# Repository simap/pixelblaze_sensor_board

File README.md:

Pixelblaze Sensor Expansion Board
-------------------

* A microphone and signal processing with frequency magnitude data ranging from 37Hz-10KHz designed to work in very loud environments
* A 3-axis 16G accelerometer
* An ambient light sensor
* 5 analog inputs that can be used with potentiometers or other analog inputs

[For sale on Tindie](https://www.tindie.com/products/12158/)! Pick up this board and/or a Pixelblaze! Make cool sound-reactive LED things, or get one and hack the firmware!

I hope you find this useful or interesting. Maybe you hack your board? I'd be stoked to hear about it! Roll your own? Great! Turn it into a robot brain? Awesome!

Shout out to Sparkfun, their boards were used in the initial prototype, and their Eagle files were really helpful!

Shout out to [https://github.com/pyrohaz/STM32F0-PCD8544GraphicAnalyzer](https://github.com/pyrohaz/STM32F0-PCD8544GraphicAnalyzer) which does similar FFT stuff with a similar processor, even shares the fixed point FFT code in common!

Non-Pixelblaze Usage
-------------------
Looking to use this with an Arduino or Teensy or something? You just need a free serial port at 115200 baud.

The protocol is fairly simple:

1. Each frame starts with "SB1.0" including a null character (6 bytes).
2. The frequency information follows, as 32 x 16-bit unsigned integers.
3. Then is the audio energy average, max frequency magnitiude, max frequency Hz, all 3 as 16-bit unsigned ints.
4. Next the accelerometer information as 3 x 16-bit signed integers.
5. The data from the Light sensor is next, as a single 16-bit unsigned integer.
6. Followed by the 5 x 16-bit analog inputs (12-bit resolution, shifted up to 16 bits)
7. Finally "END" including a null character (4 bytes).

License Information
-------------------
The hardware files are released under [Creative Commons ShareAlike 4.0 International](https://creativecommons.org/licenses/by-sa/4.0/) since the PCB is largely based off of Sparkfun boards with this license requirement.

Distributed as-is; no warranty is given.

The ElectroMage logo and wizard character is excluded from this license.

The software is released under The MIT License.

The MIT License

Copyright (c) 2018 Ben Hencke

Permission is hereby granted, free of charge, to any person obtaining a copy
of this software and associated documentation files (the "Software"), to deal
in the Software without restriction, including without limitation the rights
to use, copy, modify, merge, publish, distribute, sublicense, and/or sell
copies of the Software, and to permit persons to whom the Software is
furnished to do so, subject to the following conditions:

The above copyright notice and this permission notice shall be included in
all copies or substantial portions of the Software.

THE SOFTWARE IS PROVIDED "AS IS", WITHOUT WARRANTY OF ANY KIND, EXPRESS OR
IMPLIED, INCLUDING BUT NOT LIMITED TO THE WARRANTIES OF MERCHANTABILITY,
FITNESS FOR A PARTICULAR PURPOSE AND NONINFRINGEMENT. IN NO EVENT SHALL THE
AUTHORS OR COPYRIGHT HOLDERS BE LIABLE FOR ANY CLAIM, DAMAGES OR OTHER
LIABILITY, WHETHER IN AN ACTION OF CONTRACT, TORT OR OTHERWISE, ARISING FROM,
OUT OF OR IN CONNECTION WITH THE SOFTWARE OR THE USE OR OTHER DEALINGS IN
THE SOFTWARE.

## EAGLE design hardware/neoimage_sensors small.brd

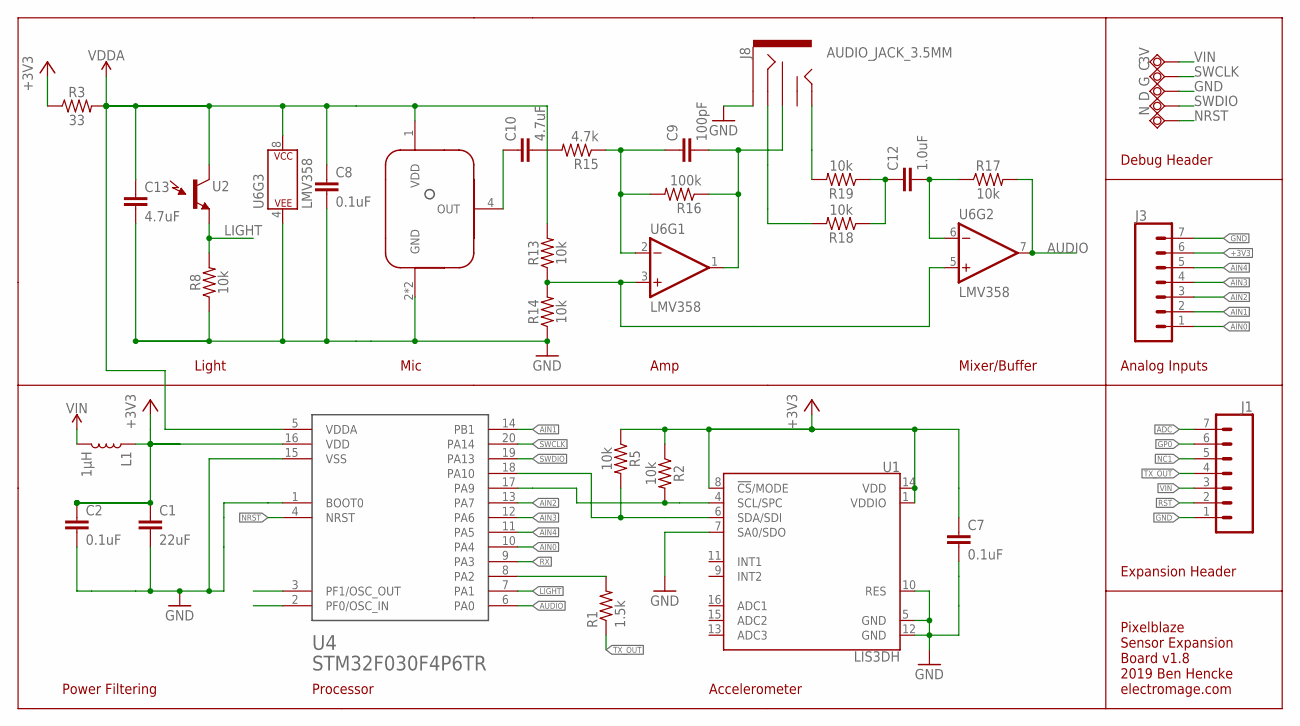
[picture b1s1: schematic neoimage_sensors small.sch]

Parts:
3V: TPSQTP18SQ; TP18SQ
C: TPSQTP18SQ; TP18SQ
C1: 22uF; 0805
C2, C7, C8: 0.1uF; 0603
C9: 100pF; 0603
C10, C13: 4.7uF; 0603
C12: 1.0uF; 0603
D: TPSQTP18SQ; TP18SQ
G: TPSQTP18SQ; TP18SQ
J1, J3: CONN_07LOCK; 1X07_LOCK
J8: AUDIO_JACK_3.5MM; AUDIO-JACK-KIT
L1: 1µH; 0805
N: TPSQTP18SQ; TP18SQ
R1: 1.5k; 0603
R2, R5, R8, R13, R14, R17, R18, R19: 10k; 0603
R3: 33; 0603
R15: 4.7k; 0603
R16: 100k; 0603
U1: LIS3DH; LGA-16-3X3
U2: LIGHT_SENSORALS; ALS-PT19
U4: STM32F030F4P6TR; TSSOP-20
U6: LMV358; SO08
U$3: MICROPHONE-MEMS; MICROPHONE-MEMS-3X3.75

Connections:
+3V3: C1.1, C2.1, C7.1, J3.6, L1.1, R2.1, R3.1, R5.1, U1.1 (VDDIO), U1.8 (!CS!/MODE), U1.14 (VDD), U4.16 (VDD)
ADC: J1.7
AIN0: J3.1, U4.10 (PA4)
AIN1: J3.2, U4.14 (PB1)
AIN2: J3.3, U4.13 (PA7)
AIN3: J3.4, U4.12 (PA6)
AIN4: J3.5, U4.11 (PA5)
AUDIO: R17.2, U4.6 (PA0), U6.7 (OUT)
GND: C1.2, C2.2, C7.2, C8.2, C13.2, G.TP, J1.1, J3.7, J8.SLEEVE, R8.1, R14.1, U1.5 (GND), U1.7 (SA0/SDO), U1.10 (RES), U1.12 (GND), U4.1 (BOOT0), U4.15 (VSS), U6.4 (P$V-), U$3.2 (GND), U$3.3 (GND)
GP0: J1.6
LIGHT: R8.2, U2.E (E1), U4.7 (PA1)
MICOUT: C9.2, J8.RSH, R16.1, U6.1 (OUT)
unnamed: C10.1, U$3.4 (OUT)
unnamed: C9.1, R15.1, R16.2, U6.2 (-IN)
unnamed: C10.2, R15.2
unnamed: R13.1, R14.2, U6.3 (+IN), U6.5 (+IN)
unnamed: C12.1, R18.1, R19.1
unnamed: C12.2, R17.1, U6.6 (-IN)
unnamed: J8.TIP, R19.2
unnamed: J8.RING, R18.2
NC1: J1.5
NRST: N.TP, U4.4 (NRST)
RST: J1.2
RX: U4.9 (PA3)
SCL: R5.2, U1.6 (SDA/SDI), U4.18 (PA10)
SDA: R2.2, U1.4 (SCL/SPC), U4.17 (PA9)
SWCLK: C.TP, U4.20 (PA14)
SWDIO: D.TP, U4.19 (PA13)
TX: R1.2, U4.8 (PA2)
TX_OUT: J1.4, R1.1
VDDA: C8.1, C13.1, R3.2, R13.2, U2.C (C1), U4.5 (VDDA), U6.8 (P$V+), U$3.1 (VDD)
VIN: 3V.TP, J1.3, L1.2

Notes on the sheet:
Expansion Header
Analog Inputs
Debug Header
Mic
Accelerometer
Processor
Light
Amp
Mixer/Buffer
Power Filtering
Pixelblaze Sensor Expansion Board v1.8 2019 Ben Hencke electromage.com

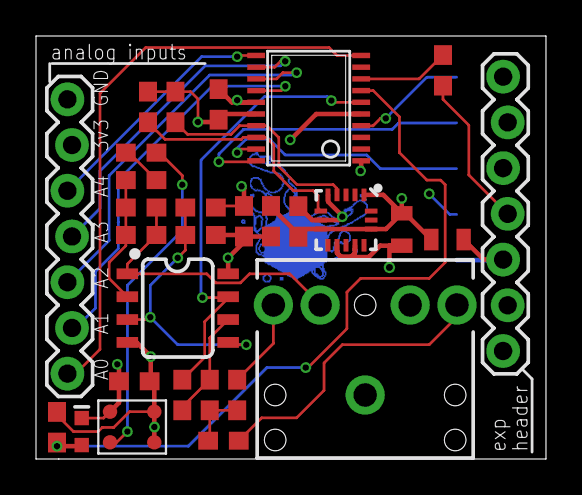
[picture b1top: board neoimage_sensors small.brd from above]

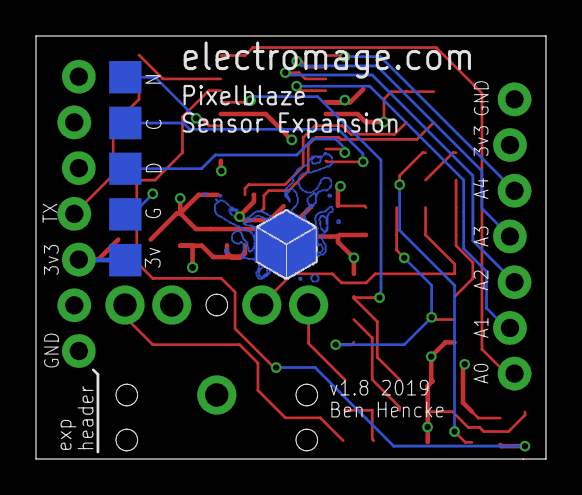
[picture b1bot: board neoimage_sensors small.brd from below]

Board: 4 copper layers, 28.3 x 23.5 mm, 35 parts (6 on the bottom side), 27 nets.

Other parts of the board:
U$4: ELECTRO_MAGE_PCB4_PIXEL_2#PNG

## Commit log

2018-02-24 initial
    works, I think!
    Timer triggers ADC, DMA collects. Store into ping-pong buffer
    FFT that, calculate magnitude.
    Hacked some efficiency - removed stdclib which freed up 1k ram (wtf?)
    just init registers directly, HAL and other drivers are quite bloated.
2018-02-28 these apparently needed also
2018-02-28 compress fft buckets using exponential curve, accelerometer
2018-02-28 break out processing stuff to another file, WIP
2018-03-11 working with output to PB
2018-03-13 add another fft for low frequency stuff, refactor lots
    downsample the 20khz to 400hz and run that through fft to get
    more depth around 12.5-162.5hz range
    tried a bunch of digital filters on downsampling, but didn't seem to
    make a difference in aliasing. simple average works about the same.
2018-03-13 remove ref to the iir filter
2018-04-15 simplify downsampler, bug in maxfrequency stuff
2018-05-07 fixes and stuff
2018-05-11 v1.0
2018-05-12 board files
2018-05-12 cleanup
2018-05-12 readme
2018-05-12 more readme and license info
2018-05-12 more readmes
2018-05-12 store link
2019-07-16 v1.8 of board
    switch to 0603, fix analog, labels
2019-07-26 switch analog input order
2019-07-26 labels for panel
2019-07-26 cleanup schematic, name signals, pdf
2019-07-26 image
2021-08-28 Add light sensor data to description of protocol
    The written description of the serial protocol was missing the information for the analog light sensor - this adds a new line to include it, as specified in the source code.
2022-07-06 add in a few more IDE files after upgrading to stm32cubeIDE

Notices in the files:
parts and their libraries:
SparkFun-Connectors: Licensing: Creative Commons ShareAlike 4.0 International - https://creativecommons.org/licenses/by-sa/4.0
